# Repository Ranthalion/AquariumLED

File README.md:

View this project on [CADLAB.io](https://cadlab.io/project/1243). 

AquariumLED
===========

LED Lighting system for marine aquarium

Execute RunServer in the Application folder to start the server and view the page.

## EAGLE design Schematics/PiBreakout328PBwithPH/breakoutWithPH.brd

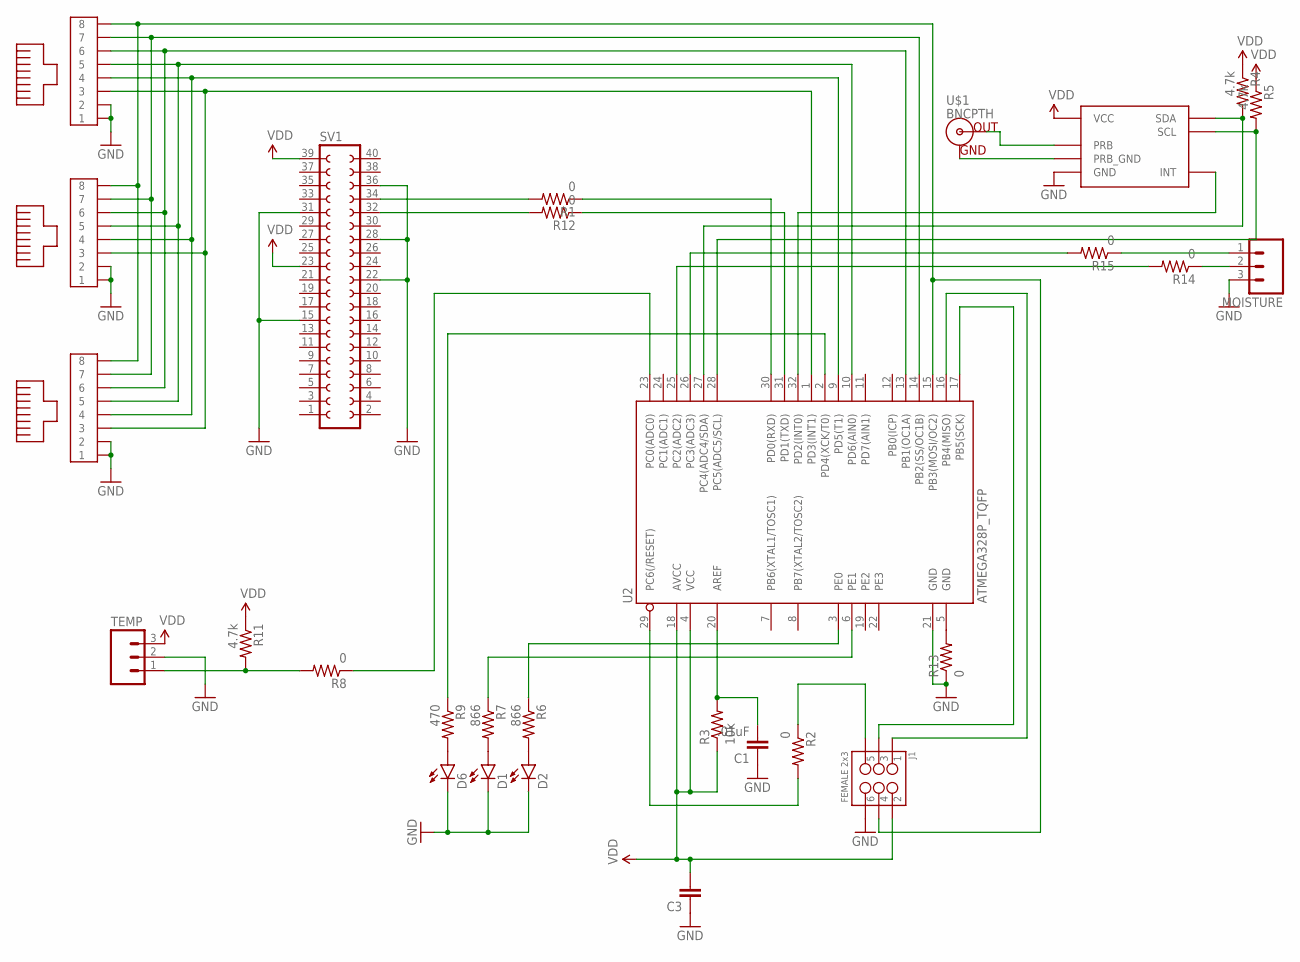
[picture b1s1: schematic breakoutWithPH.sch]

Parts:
C1: .01uF; 1206
C3: CAP1206; 1206
D1, D2, D6: LED0603; LED-0603
J1: FEMALE 2x3; 2X3
MOISTURE: M03LOCK_LONGPADS; 1X03_LOCK_LONGPADS
R1, R2, R8, R12, R13, R14, R15: 0; 1206
R3: 10k; 1206
R4, R5, R11: 4.7k; 1206
R6, R7: 866; 1206
R9: 470; 1206
SV1: FE20-2
TEMP: M03LOCK_LONGPADS; 1X03_LOCK_LONGPADS
U1: PH_SMD
U2: ATMEGA328P_TQFP; TQFP32-08
U$1: BNCPTH; BNC
U$2, U$3, U$4: MOLEX-RJ45-SMT

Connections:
GND: C1.1, C3.1, D1.C, D2.C, D6.C, J1.6, MOISTURE.3, R13.1, SV1.15, SV1.22, SV1.28, SV1.31, SV1.36, TEMP.2, U1.6 (GND), U2.21 (GND), U$2.1, U$2.2, U$3.1, U$3.2, U$4.1, U$4.2
unnamed: R12.1, U2.31 (PD1(TXD))
unnamed: J1.5, R2.1
unnamed: U2.9 (PD5(T1)), U$2.4, U$3.4, U$4.4
unnamed: U2.1 (PD3(INT1)), U$2.3, U$3.3, U$4.3
unnamed: J1.4, U2.15 (PB3(MOSI/OC2)), U$2.8, U$3.8, U$4.8
unnamed: U2.10 (PD6(AIN0)), U$2.5, U$3.5, U$4.5
unnamed: D2.A, R6.2
unnamed: R2.2, U2.29 (PC6(/RESET))
unnamed: R9.1, U2.2 (PD4(XCK/T0))
unnamed: R1.1, U2.30 (PD0(RXD))
unnamed: J1.3, U2.17 (PB5(SCK))
unnamed: U2.13 (PB1(OC1A)), U$2.6, U$3.6, U$4.6
unnamed: U2.14 (PB2(SS/OC1B)), U$2.7, U$3.7, U$4.7
unnamed: J1.1, U2.16 (PB4(MISO))
unnamed: R6.1, U2.3 (PE0)
unnamed: U1.7 (INT), U2.32 (PD2(INT0))
unnamed: R7.1, U2.6 (PE1)
unnamed: D1.A, R7.2
unnamed: R1.2, SV1.34
unnamed: D6.A, R9.2
unnamed: C1.2, R3.2, U2.20 (AREF)
unnamed: R8.1, U2.23 (PC0(ADC0))
unnamed: R8.2, R11.2, TEMP.1
unnamed: R5.2, U1.8 (SCL), U2.28 (PC5(ADC5/SCL))
unnamed: R4.2, U1.1 (SDA), U2.27 (PC4(ADC4/SDA))
unnamed: R12.2, SV1.32
unnamed: R13.2, U2.5 (GND)
unnamed: U1.4 (PRB), U$1.S (OUT)
unnamed: R15.2, U2.26 (PC3(ADC3))
unnamed: R14.2, U2.25 (PC2(ADC2))
unnamed: MOISTURE.2, R14.1
unnamed: MOISTURE.1, R15.1
PRB_GND: U1.5 (PRB_GND), U$1.GND
VDD: C3.2, J1.2, R3.1, R4.1, R5.1, R11.1, SV1.23, SV1.39, TEMP.3, U1.3 (VCC), U2.4 (VCC), U2.18 (AVCC)

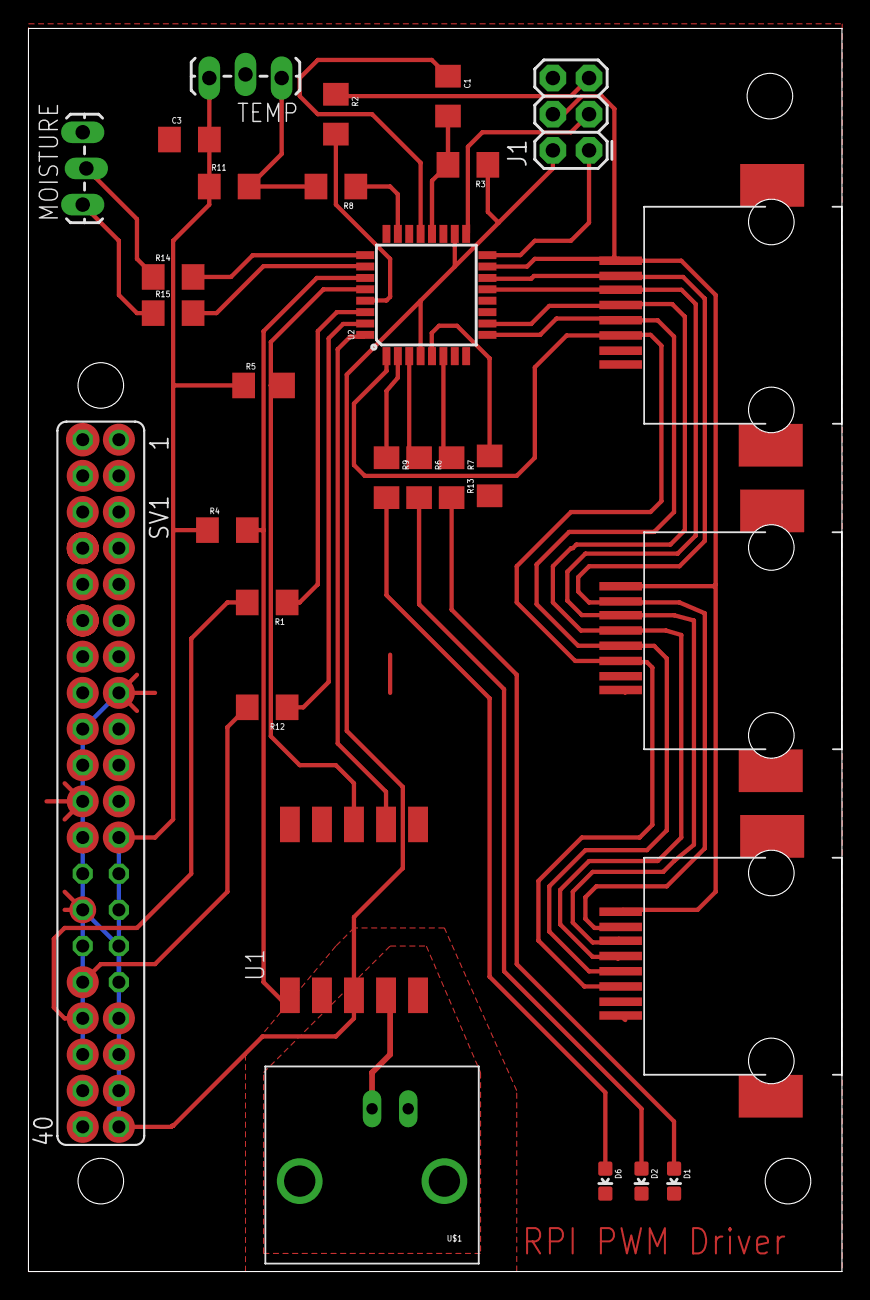
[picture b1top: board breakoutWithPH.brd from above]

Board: 2 copper layers, 57.1 x 87.3 mm, 29 parts (0 on the bottom side), 35 nets.

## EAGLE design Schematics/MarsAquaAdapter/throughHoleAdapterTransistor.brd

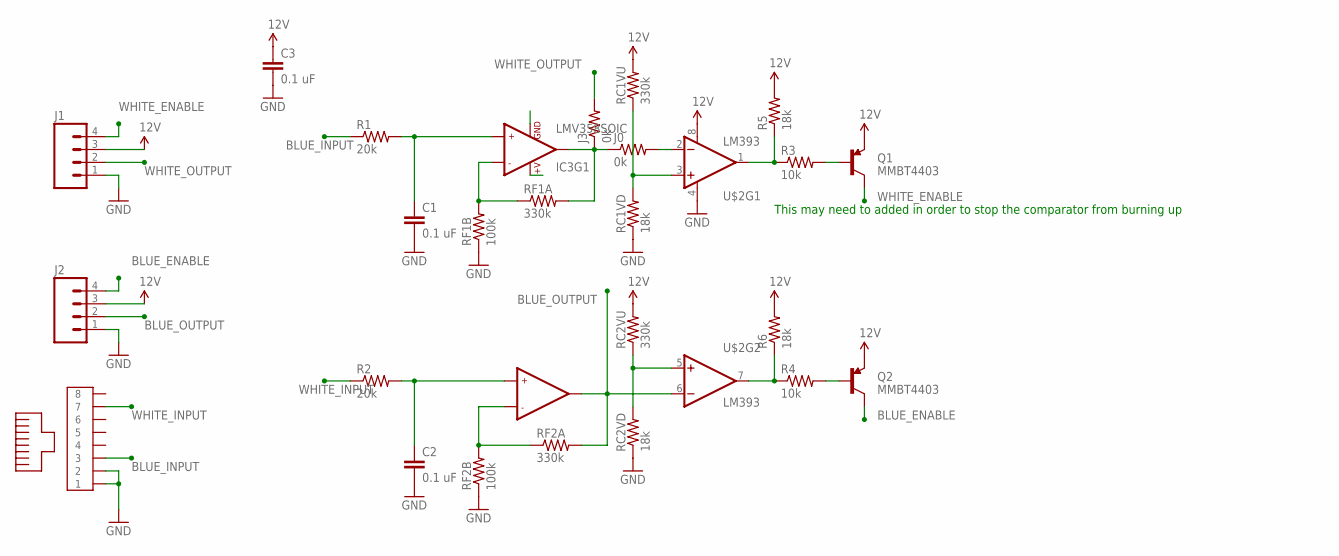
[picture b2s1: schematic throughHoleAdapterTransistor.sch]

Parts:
C1, C2, C3: 0.1 uF; 1206
IC3: LMV358SOIC; SO08
J0, J3: 0k; 1206
J1, J2: M04LONGPADS; 1X04_LONGPADS
Q1, Q2: MMBT4403; SOT23-3
R1, R2: 20k; 1206
R3, R4: 10k; 1206
R5, R6: 18k; 1206
RC1VD, RC2VD: 18k; 1206
RC1VU, RC2VU: 330k; 1206
RF1A, RF2A: 330k; 1206
RF1B, RF2B: 100k; 1206
U$1: MOLEX-RJ45-SMT
U$2: LM393; SO08

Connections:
12V: C3.1, IC3.8 (+V), J1.3, J2.3, Q1.2 (E), Q2.2 (E), R5.2, R6.2, RC1VU.2, RC2VU.2, U$2.8 (V+)
BLUE_ENABLE: J2.4, Q2.3 (C)
BLUE_INPUT: R1.1, U$1.3
BLUE_OUTPUT: IC3.7 (OUT2), J2.2, RF2A.2, U$2.6 (-IN)
GND: C1.2, C2.2, C3.2, IC3.4 (GND), J1.1, J2.1, RC1VD.1, RC2VD.1, RF1B.1, RF2B.1, U$1.1, U$1.2, U$2.4 (V-)
unnamed: Q2.1 (B), R4.2
unnamed: J0.2, U$2.2 (-IN)
unnamed: R3.1, R5.1, U$2.1 (OUT)
unnamed: IC3.2 (-IN1), RF1A.1, RF1B.2
unnamed: RC2VD.2, RC2VU.1, U$2.5 (+IN)
unnamed: IC3.6 (-IN2), RF2A.1, RF2B.2
unnamed: C1.1, IC3.3 (+IN1), R1.2
unnamed: C2.1, IC3.5 (+IN2), R2.2
unnamed: RC1VD.2, RC1VU.1, U$2.3 (+IN)
unnamed: Q1.1 (B), R3.2
unnamed: R4.1, R6.1, U$2.7 (OUT)
WHITE_ENABLE: J1.4, Q1.3 (C)
WHITE_INPUT: R2.1, U$1.7
WHITE_OUTPUT: J1.2, J3.2
WHITE_OUTPUT_TEMP: IC3.1 (OUT1), J0.1, J3.1, RF1A.2

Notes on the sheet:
This may need to added in order to stop the comparator from burning up

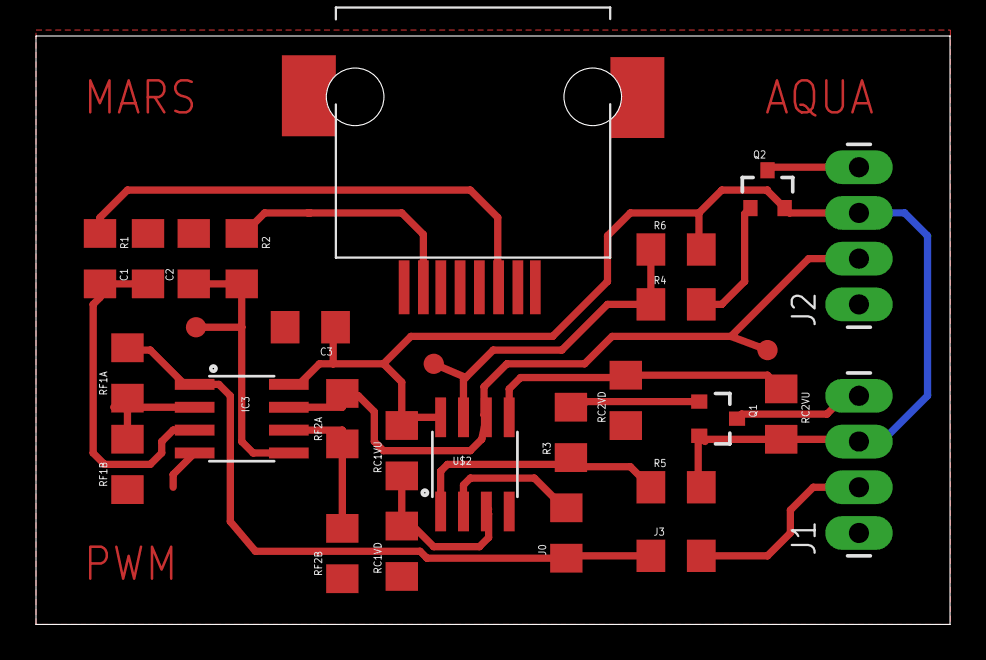
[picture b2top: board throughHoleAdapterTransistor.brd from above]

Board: 2 copper layers, 50.8 x 32.7 mm, 26 parts (0 on the bottom side), 20 nets.

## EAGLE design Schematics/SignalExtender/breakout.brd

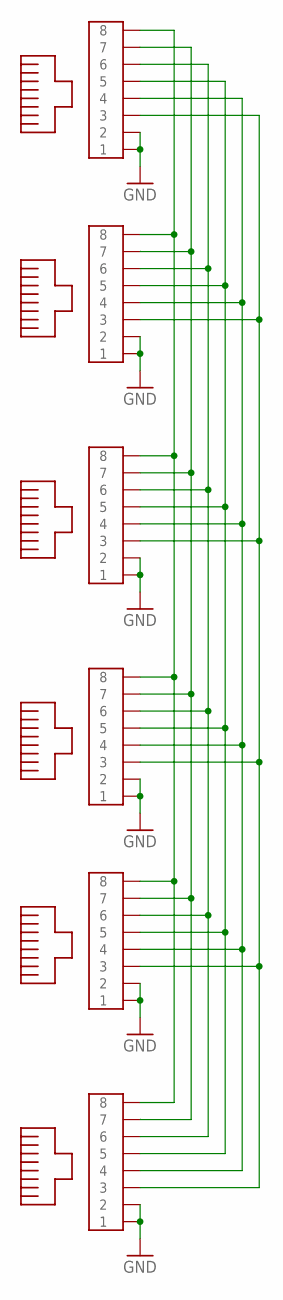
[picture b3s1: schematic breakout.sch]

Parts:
U$1, U$2, U$3, U$4, U$5, U$6: MOLEX-RJ45-SMT

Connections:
GND: U$1.1, U$1.2, U$2.1, U$2.2, U$3.1, U$3.2, U$4.1, U$4.2, U$5.1, U$5.2, U$6.1, U$6.2
unnamed: U$1.4, U$2.4, U$3.4, U$4.4, U$5.4, U$6.4
unnamed: U$1.3, U$2.3, U$3.3, U$4.3, U$5.3, U$6.3
unnamed: U$1.5, U$2.5, U$3.5, U$4.5, U$5.5, U$6.5
unnamed: U$1.8, U$2.8, U$3.8, U$4.8, U$5.8, U$6.8
unnamed: U$1.6, U$2.6, U$3.6, U$4.6, U$5.6, U$6.6
unnamed: U$1.7, U$2.7, U$3.7, U$4.7, U$5.7, U$6.7

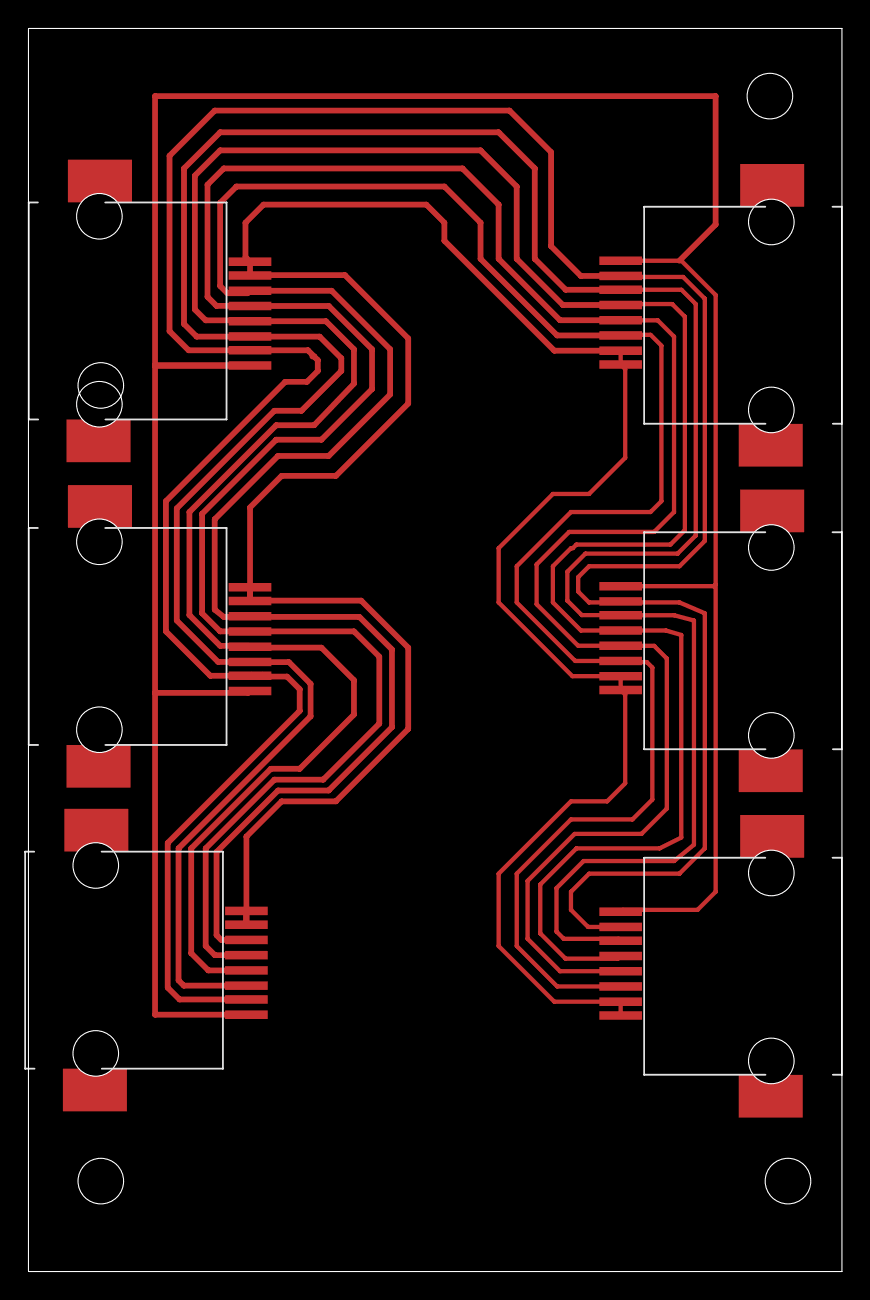
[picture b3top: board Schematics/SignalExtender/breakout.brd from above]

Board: 2 copper layers, 57.1 x 87.3 mm, 6 parts (0 on the bottom side), 7 nets.

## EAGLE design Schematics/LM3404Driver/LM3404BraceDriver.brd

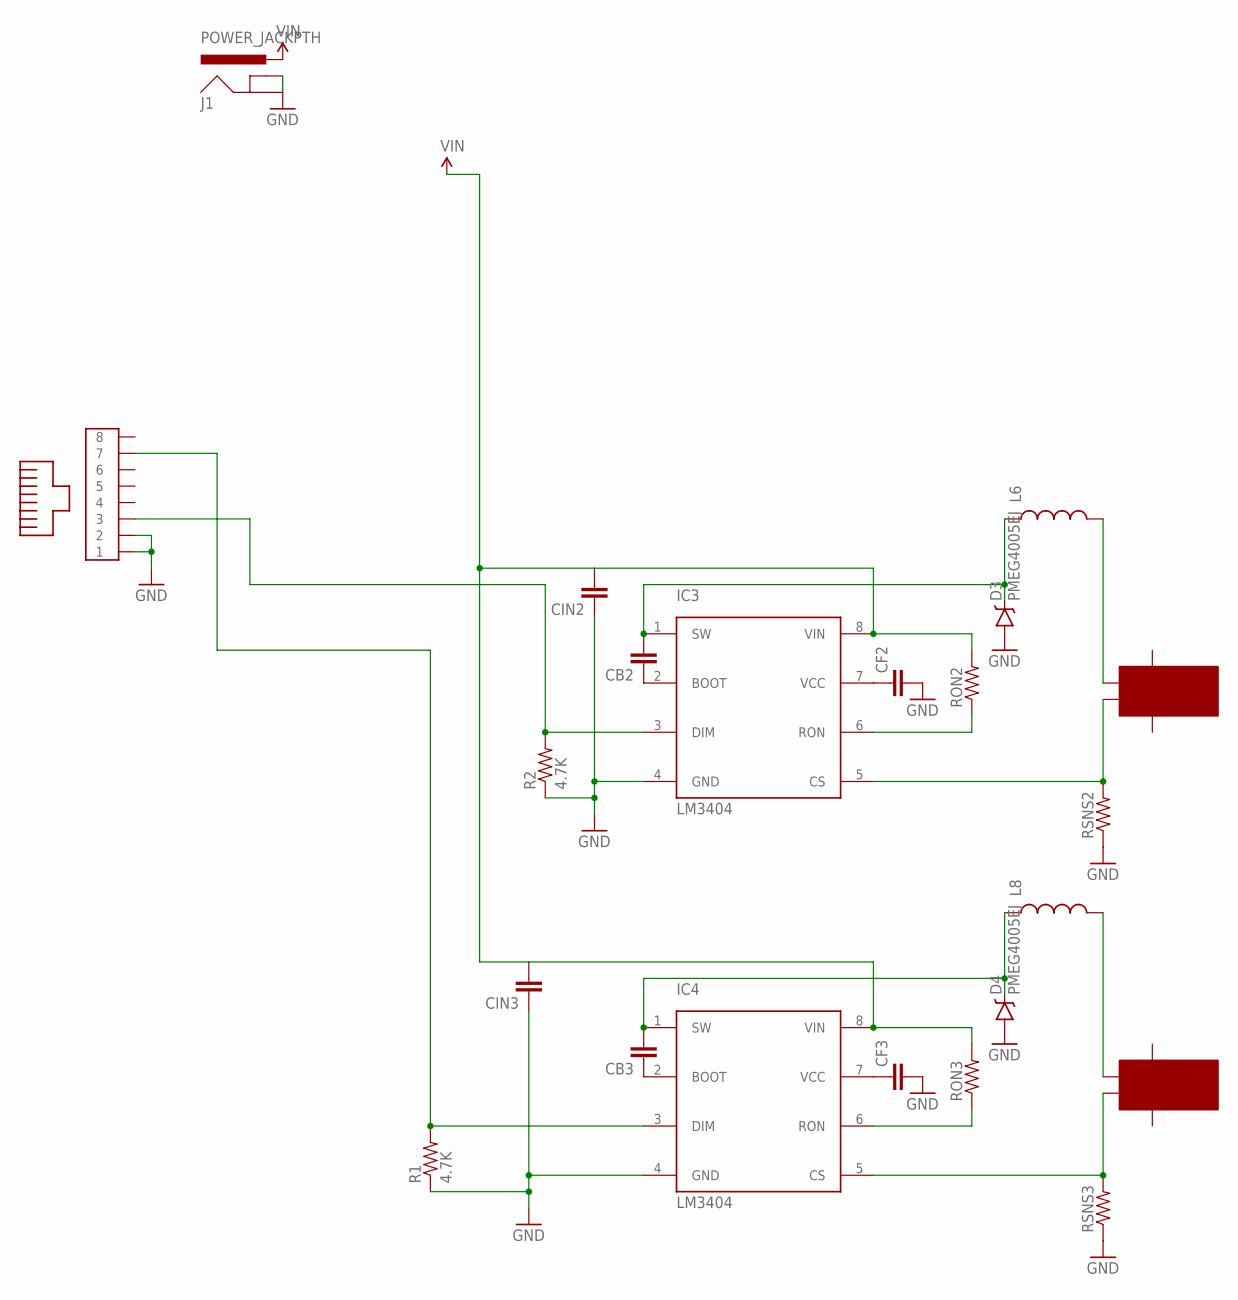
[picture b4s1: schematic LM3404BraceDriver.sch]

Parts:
CB2, CB3: CAP0603-CAP; 0603-CAP
CF2, CF3: CAP1206; 1206
CIN2, CIN3: CAP1210; 1210
D3, D4: PMEG4005EJ; SOD-323
IC3, IC4: LM3404; SO8
J1: POWER_JACKPTH; POWER_JACK_PTH
L6, L8: INDUCTORSDR1105; B82462G
R1, R2: 4.7K; 1206
RON2, RON3: RESISTOR1206; 1206
RSNS2, RSNS3: RESISTOR1206; 1206
U$1: MOLEX-RJ45-SMT
U$5, U$6: RCA_JACK

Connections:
GND: CF2.2, CF3.2, CIN2.1, CIN3.1, D3.A, D4.A, IC3.4 (GND), IC4.4 (GND), J1.GND, J1.GNDBREAK, R1.1, R2.1, RSNS2.1, RSNS3.1, U$1.1, U$1.2
unnamed: IC3.3 (DIM), R2.2, U$1.3
unnamed: CF2.1, IC3.7 (VCC)
unnamed: CB2.1, IC3.2 (BOOT)
unnamed: CB2.2, D3.C, IC3.1 (SW), L6.P$1 (1)
unnamed: IC3.6 (RON), RON2.1
unnamed: IC3.5 (CS), RSNS2.2, U$6.INNER
unnamed: L6.P$2 (2), U$6.SIG
unnamed: IC4.3 (DIM), R1.2, U$1.7
unnamed: CF3.1, IC4.7 (VCC)
unnamed: CB3.1, IC4.2 (BOOT)
unnamed: CB3.2, D4.C, IC4.1 (SW), L8.P$1 (1)
unnamed: IC4.6 (RON), RON3.1
unnamed: IC4.5 (CS), RSNS3.2, U$5.INNER
unnamed: L8.P$2 (2), U$5.SIG
VIN: CIN2.2, CIN3.2, IC3.8 (VIN), IC4.8 (VIN), J1.PWR, RON2.2, RON3.2

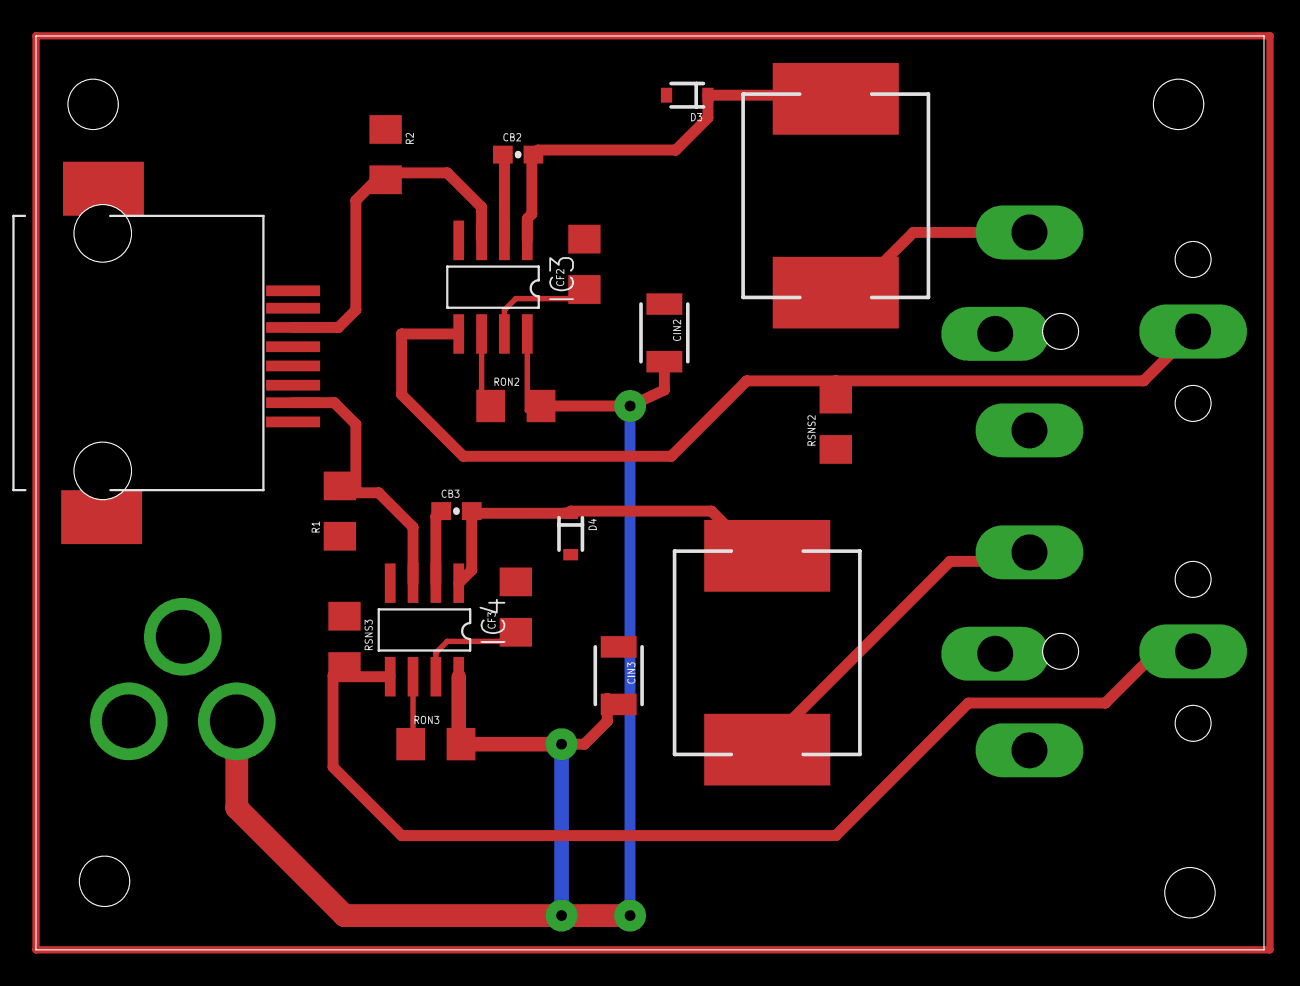
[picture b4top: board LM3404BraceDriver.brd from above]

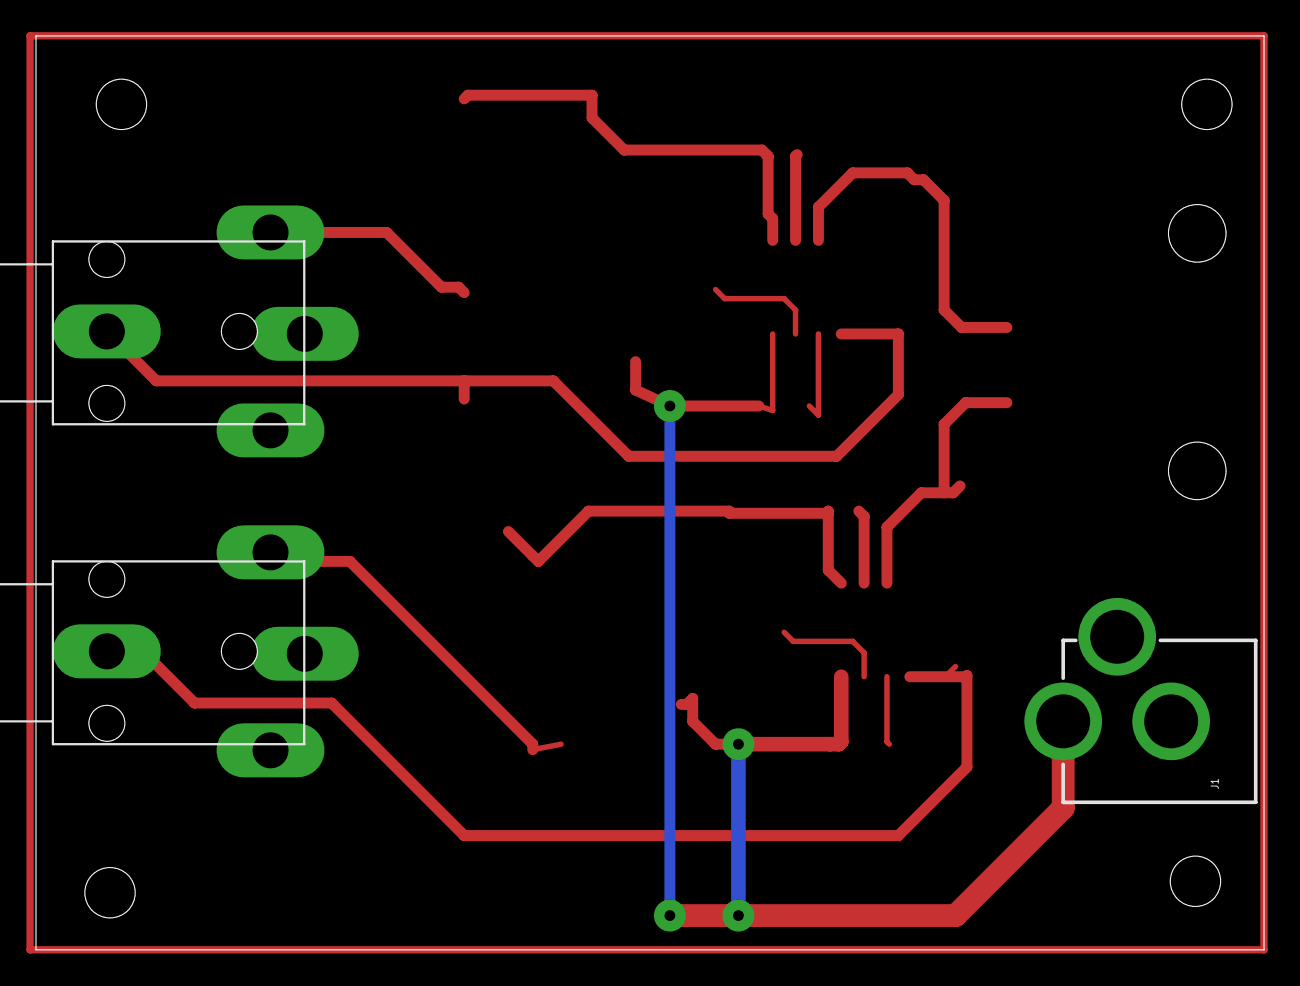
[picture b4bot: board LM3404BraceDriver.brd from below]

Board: 2 copper layers, 68.2 x 50.8 mm, 22 parts (3 on the bottom side), 16 nets.

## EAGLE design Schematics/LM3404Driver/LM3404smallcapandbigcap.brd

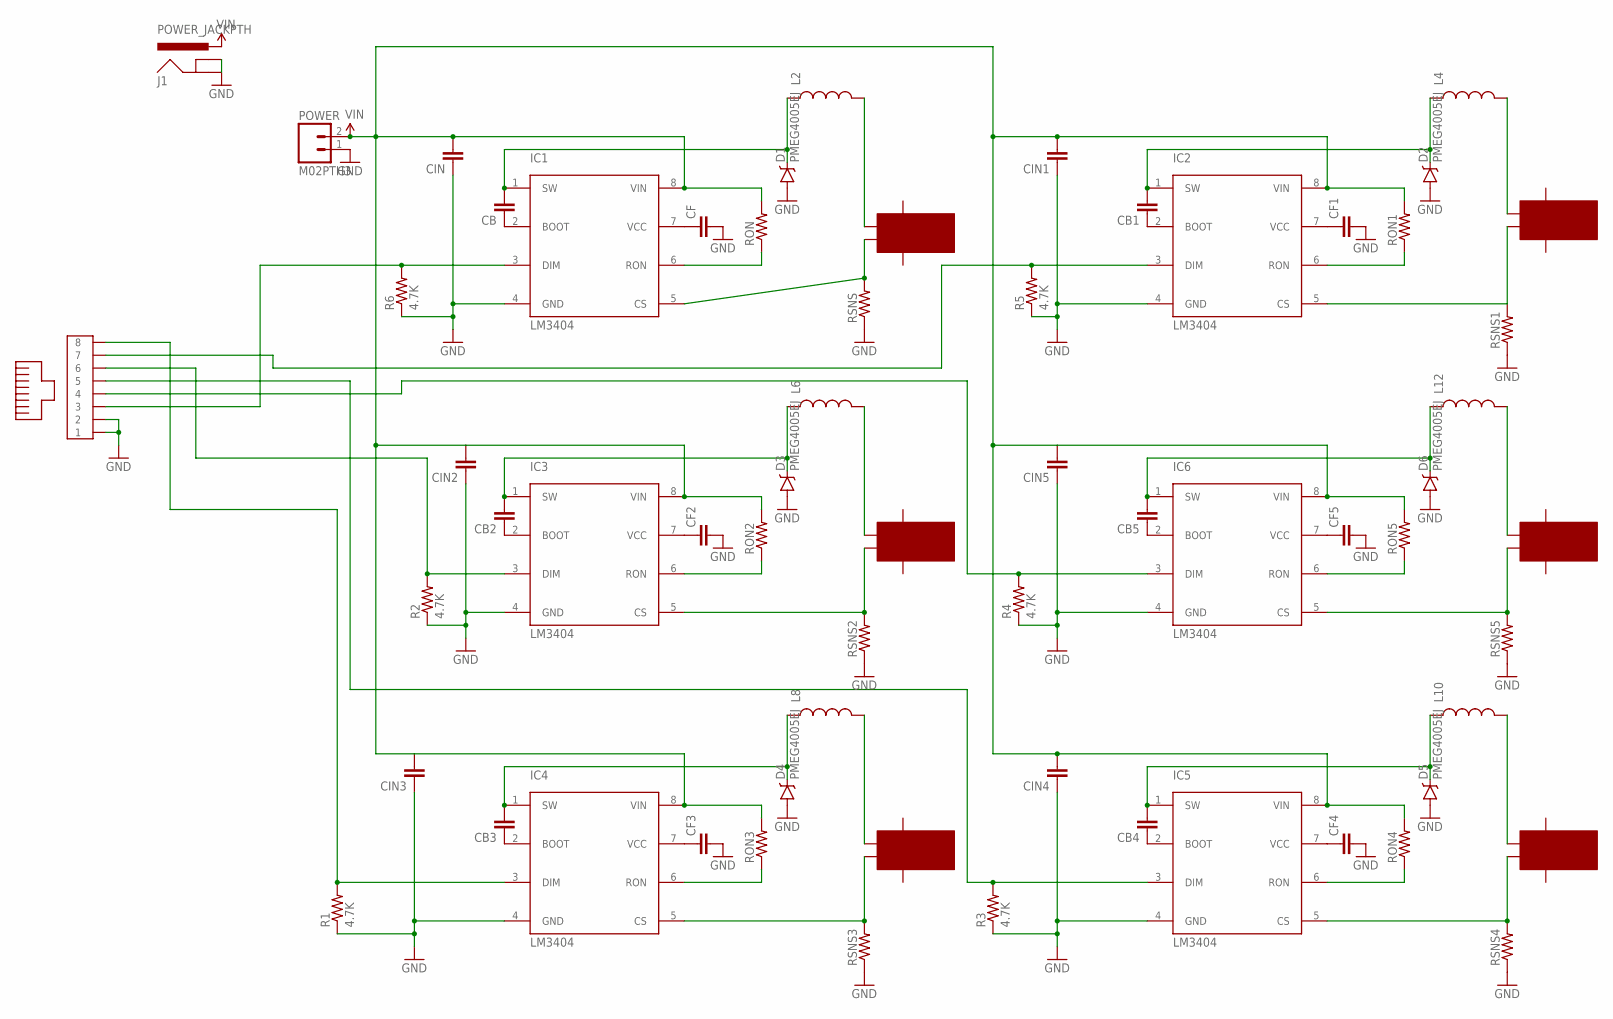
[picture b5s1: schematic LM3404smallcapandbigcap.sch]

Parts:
CB, CB1, CB2, CB3, CB4, CB5: CAP0603-CAP; 0603-CAP
CF, CF1, CF2, CF3, CF4, CF5: CAP1206; 1206
CIN, CIN1, CIN2, CIN3, CIN4, CIN5: CAP1210; 1210
D1, D2, D3, D4, D5, D6: PMEG4005EJ; SOD-323
IC1, IC2, IC3, IC4, IC5, IC6: LM3404; SO8
J1: POWER_JACKPTH; POWER_JACK_PTH
L2, L4, L6, L8, L10, L12: INDUCTORSDR1105; B82462G
POWER: M02PTH3; 1X02_LONGPADS
R1, R2, R3, R4, R5, R6: 4.7K; 1206
RON, RON1, RON2, RON3, RON4, RON5: RESISTOR1206; 1206
RSNS, RSNS1, RSNS2, RSNS3, RSNS4, RSNS5: RESISTOR1206; 1206
U$1: MOLEX-RJ45-SMT
U$2, U$3, U$4, U$5, U$6, U$7: RCA_JACK

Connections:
GND: CF.2, CF1.2, CF2.2, CF3.2, CF4.2, CF5.2, CIN.1, CIN1.1, CIN2.1, CIN3.1, CIN4.1, CIN5.1, D1.A, D2.A, D3.A, D4.A, D5.A, D6.A, IC1.4 (GND), IC2.4 (GND), IC3.4 (GND), IC4.4 (GND), IC5.4 (GND), IC6.4 (GND), J1.GND, J1.GNDBREAK, POWER.1, R1.1, R2.1, R3.1, R4.1, R5.1, R6.1, RSNS.1, RSNS1.1, RSNS2.1, RSNS3.1, RSNS4.1, RSNS5.1, U$1.1, U$1.2
unnamed: CF.1, IC1.7 (VCC)
unnamed: CB.1, IC1.2 (BOOT)
unnamed: IC2.3 (DIM), R5.2, U$1.7
unnamed: CB.2, D1.C, IC1.1 (SW), L2.P$1 (1)
unnamed: IC1.5 (CS), RSNS.2, U$7.INNER
unnamed: IC1.6 (RON), RON.1
unnamed: CF1.1, IC2.7 (VCC)
unnamed: IC1.3 (DIM), R6.2, U$1.3
unnamed: L2.P$2 (2), U$7.SIG
unnamed: CB1.1, IC2.2 (BOOT)
unnamed: CB1.2, D2.C, IC2.1 (SW), L4.P$1 (1)
unnamed: IC2.6 (RON), RON1.1
unnamed: IC2.5 (CS), RSNS1.2, U$2.INNER
unnamed: L4.P$2 (2), U$2.SIG
unnamed: IC3.3 (DIM), R2.2, U$1.6
unnamed: CF2.1, IC3.7 (VCC)
unnamed: CB2.1, IC3.2 (BOOT)
unnamed: CB2.2, D3.C, IC3.1 (SW), L6.P$1 (1)
unnamed: IC3.6 (RON), RON2.1
unnamed: IC3.5 (CS), RSNS2.2, U$6.INNER
unnamed: L6.P$2 (2), U$6.SIG
unnamed: IC4.3 (DIM), R1.2, U$1.8
unnamed: CF3.1, IC4.7 (VCC)
unnamed: CB3.1, IC4.2 (BOOT)
unnamed: CB3.2, D4.C, IC4.1 (SW), L8.P$1 (1)
unnamed: IC4.6 (RON), RON3.1
unnamed: IC4.5 (CS), RSNS3.2, U$5.INNER
unnamed: L8.P$2 (2), U$5.SIG
unnamed: IC5.3 (DIM), R3.2, U$1.5
unnamed: CF4.1, IC5.7 (VCC)
unnamed: CB4.1, IC5.2 (BOOT)
unnamed: CB4.2, D5.C, IC5.1 (SW), L10.P$1 (1)
unnamed: IC5.6 (RON), RON4.1
unnamed: IC5.5 (CS), RSNS4.2, U$4.INNER
unnamed: L10.P$2 (2), U$4.SIG
unnamed: IC6.3 (DIM), R4.2, U$1.4
unnamed: CF5.1, IC6.7 (VCC)
unnamed: CB5.1, IC6.2 (BOOT)
unnamed: CB5.2, D6.C, IC6.1 (SW), L12.P$1 (1)
unnamed: IC6.6 (RON), RON5.1
unnamed: IC6.5 (CS), RSNS5.2, U$3.INNER
unnamed: L12.P$2 (2), U$3.SIG
VIN: CIN.2, CIN1.2, CIN2.2, CIN3.2, CIN4.2, CIN5.2, IC1.8 (VIN), IC2.8 (VIN), IC3.8 (VIN), IC4.8 (VIN), IC5.8 (VIN), IC6.8 (VIN), J1.PWR, POWER.2, RON.2, RON1.2, RON2.2, RON3.2, RON4.2, RON5.2

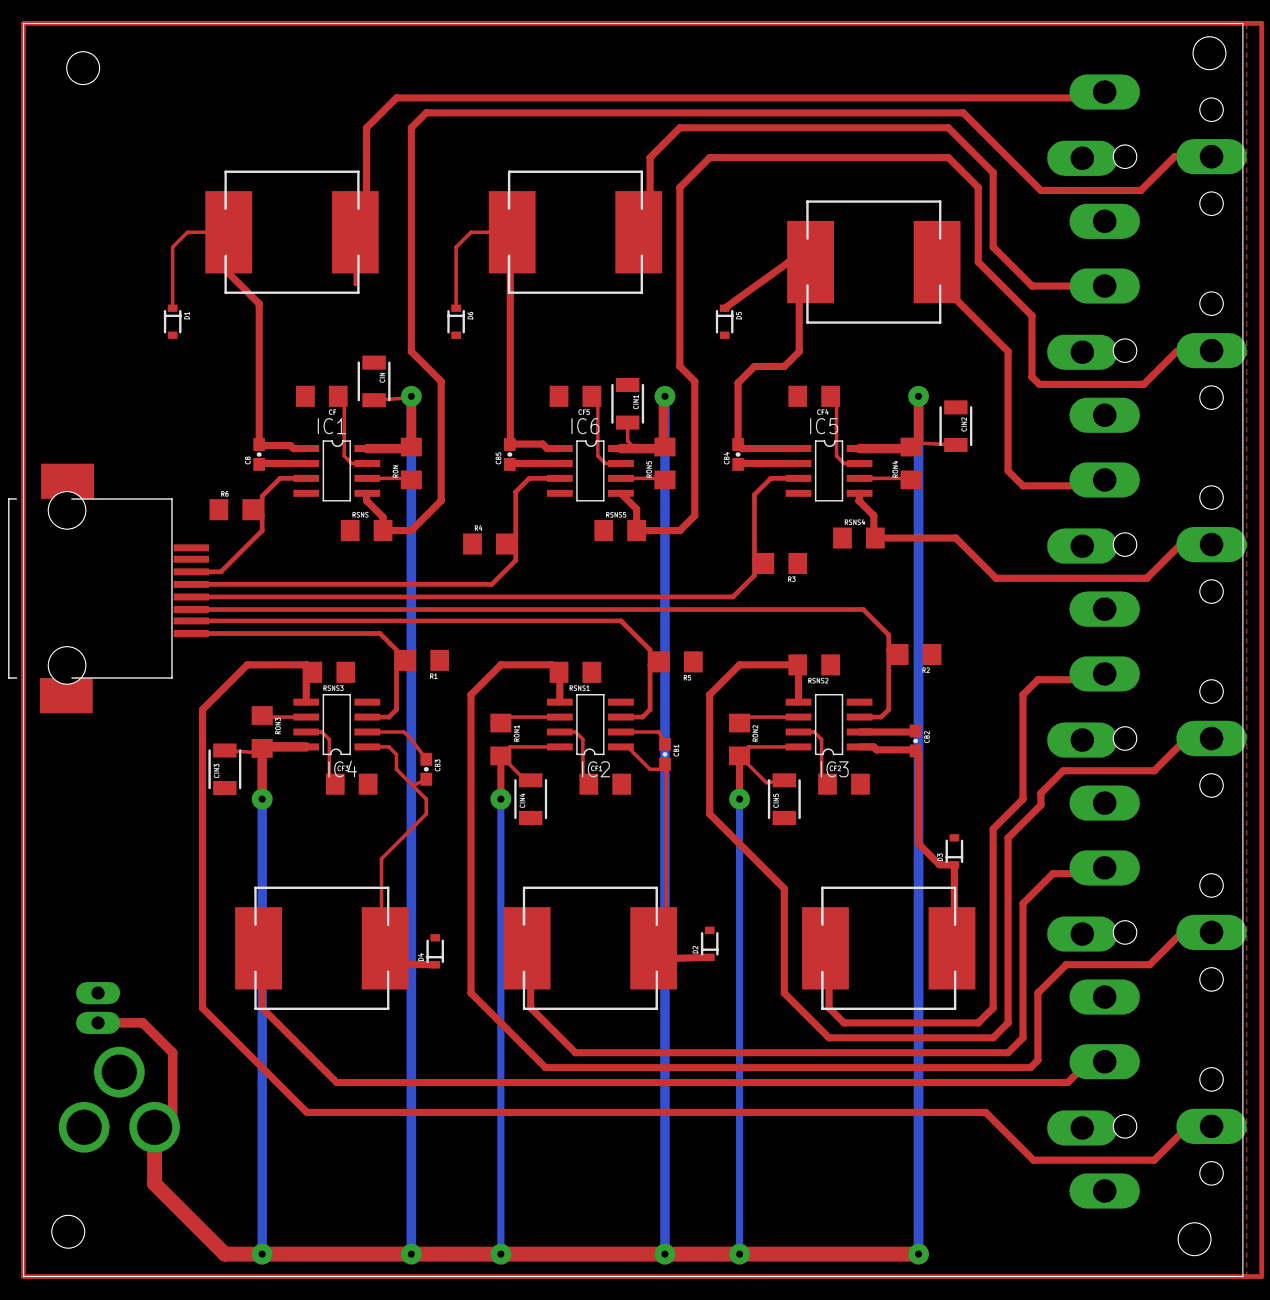
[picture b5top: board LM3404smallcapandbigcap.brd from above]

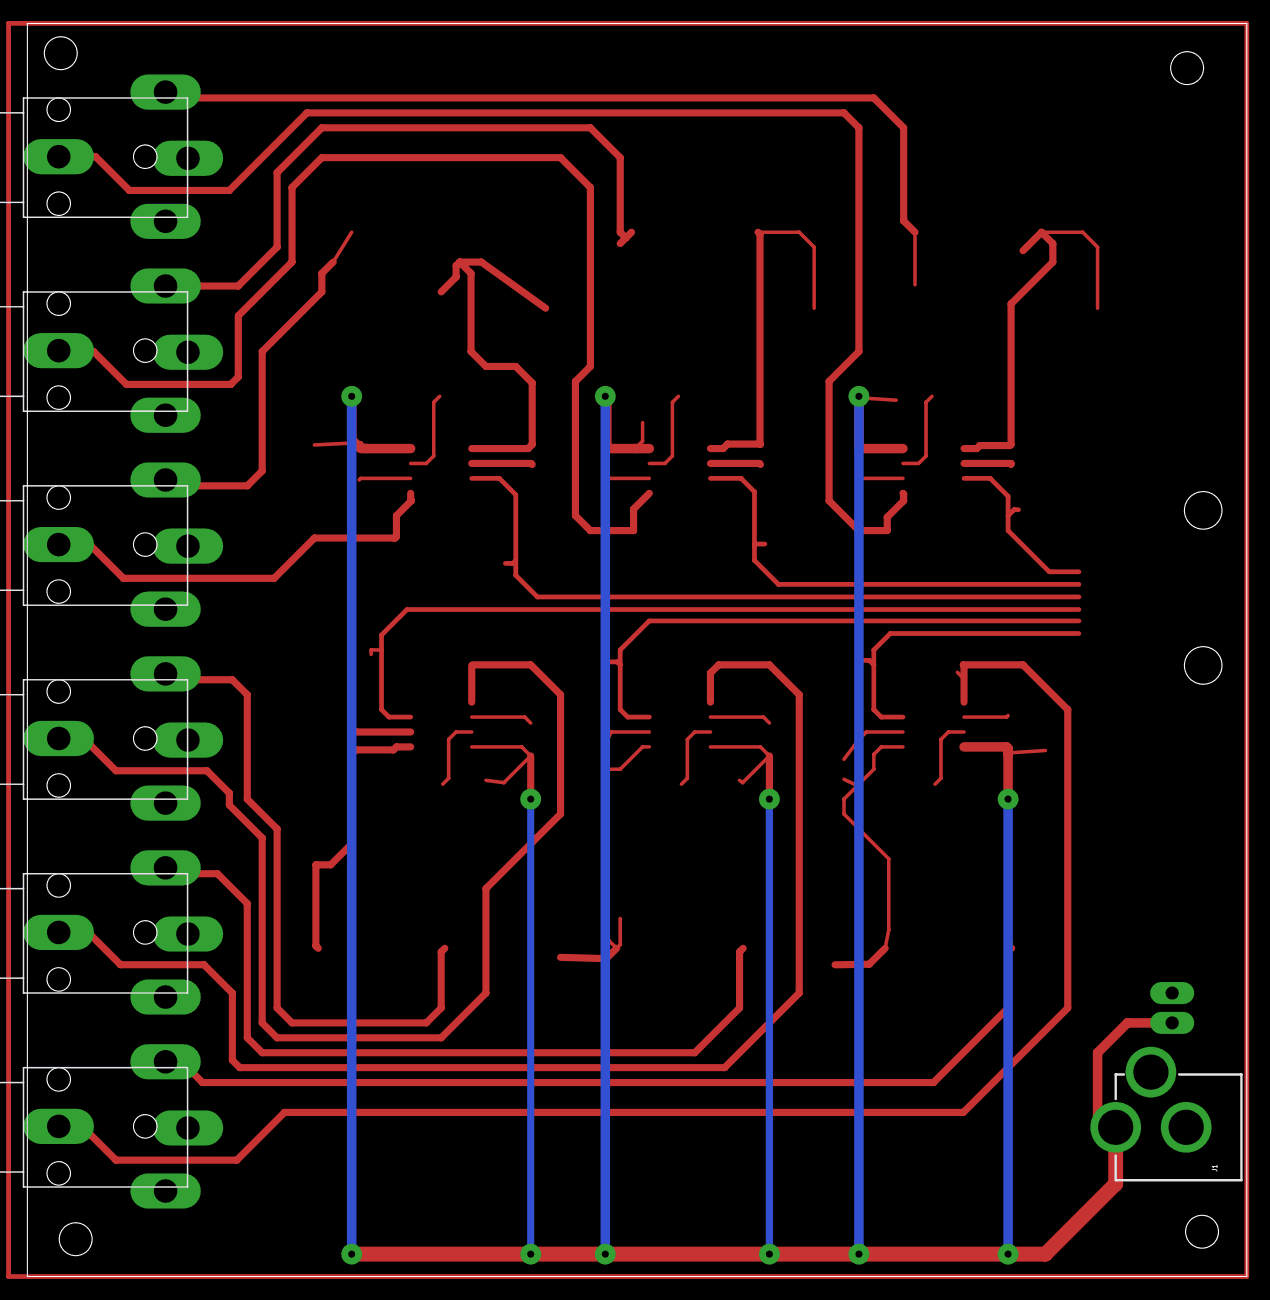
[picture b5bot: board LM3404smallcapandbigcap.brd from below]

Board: 2 copper layers, 103.8 x 106.7 mm, 63 parts (7 on the bottom side), 44 nets.

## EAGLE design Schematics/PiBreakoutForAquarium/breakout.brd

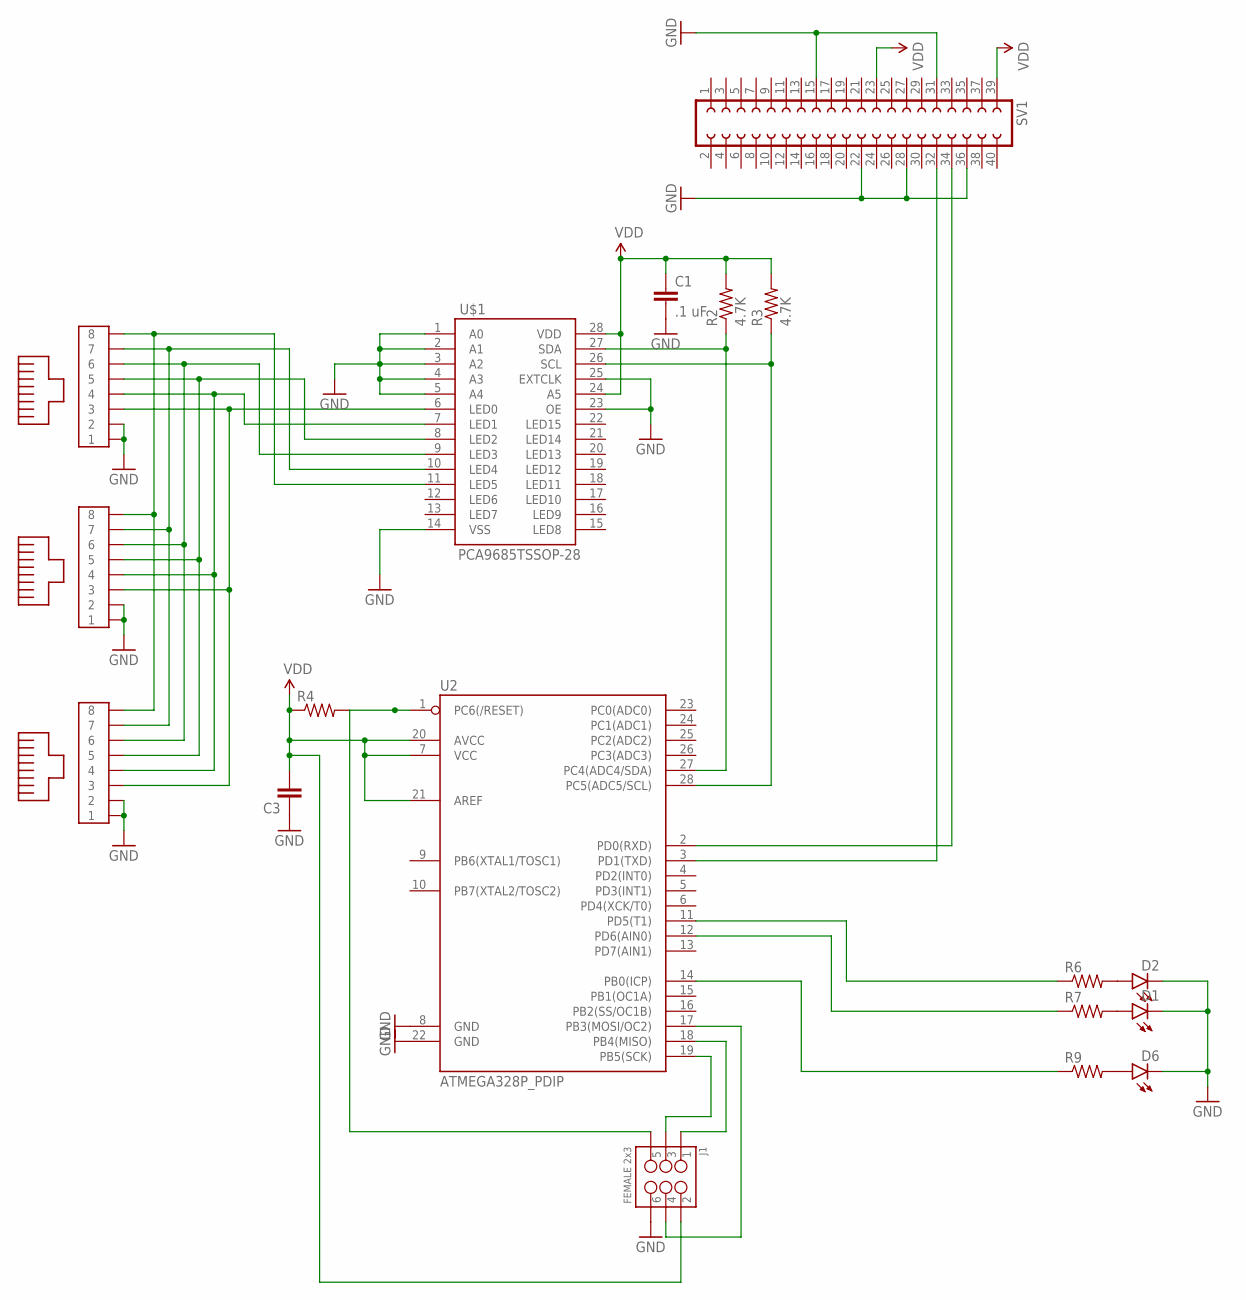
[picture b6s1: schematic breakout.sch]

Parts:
C1: .1 uF; 1206
C3: CAP1206; 1206
D1, D2, D6: LED0603; LED-0603
J1: FEMALE 2x3; 2X3
R2, R3: 4.7K; 1206
R4, R6, R7, R9: RESISTOR1206; 1206
SV1: FE20-2
U2: ATMEGA328P_PDIP; DIL28-3
U$1: PCA9685TSSOP-28; TSSOP28
U$2, U$3, U$4: MOLEX-RJ45-SMT

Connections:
GND: C1.2, C3.1, D1.C, D2.C, D6.C, J1.6, SV1.15, SV1.22, SV1.28, SV1.31, SV1.36, U2.8 (GND), U2.22 (GND), U$1.1 (A0), U$1.2 (A1), U$1.3 (A2), U$1.4 (A3), U$1.5 (A4), U$1.14 (VSS), U$1.23 (OE), U$1.25 (EXTCLK), U$2.1, U$2.2, U$3.1, U$3.2, U$4.1, U$4.2
unnamed: SV1.32, U2.3 (PD1(TXD))
unnamed: J1.5, R4.2, U2.1 (PC6(/RESET))
unnamed: U$1.6 (LED0), U$2.3, U$3.3, U$4.3
unnamed: R2.1, U2.27 (PC4(ADC4/SDA)), U$1.27 (SDA)
unnamed: D2.A, R6.2
unnamed: J1.4, U2.17 (PB3(MOSI/OC2))
unnamed: SV1.34, U2.2 (PD0(RXD))
unnamed: U$1.7 (LED1), U$2.4, U$3.4, U$4.4
unnamed: U$1.11 (LED5), U$2.8, U$3.8, U$4.8
unnamed: U$1.10 (LED4), U$2.7, U$3.7, U$4.7
unnamed: U$1.9 (LED3), U$2.6, U$3.6, U$4.6
unnamed: U$1.8 (LED2), U$2.5, U$3.5, U$4.5
unnamed: J1.1, U2.18 (PB4(MISO))
unnamed: J1.3, U2.19 (PB5(SCK))
unnamed: D1.A, R7.2
unnamed: D6.A, R9.2
unnamed: R9.1, U2.14 (PB0(ICP))
unnamed: R7.1, U2.12 (PD6(AIN0))
unnamed: R6.1, U2.11 (PD5(T1))
unnamed: R3.1, U2.28 (PC5(ADC5/SCL)), U$1.26 (SCL)
VDD: C1.1, C3.2, J1.2, R2.2, R3.2, R4.1, SV1.23, SV1.39, U2.7 (VCC), U2.20 (AVCC), U2.21 (AREF), U$1.24 (A5), U$1.28 (VDD)

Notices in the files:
parts and their libraries:
SparkFun-Connectors: Licensing: CC v3.0 Share-Alike You are welcome to use this library for commercial purposes.
SparkFun-Capacitors: Licensing: Creative Commons ShareAlike 4.0 International - https://creativecommons.org/licenses/by-sa/4.0
